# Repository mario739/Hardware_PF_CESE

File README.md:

###HARDWARE PROYECTO FINAL CESE

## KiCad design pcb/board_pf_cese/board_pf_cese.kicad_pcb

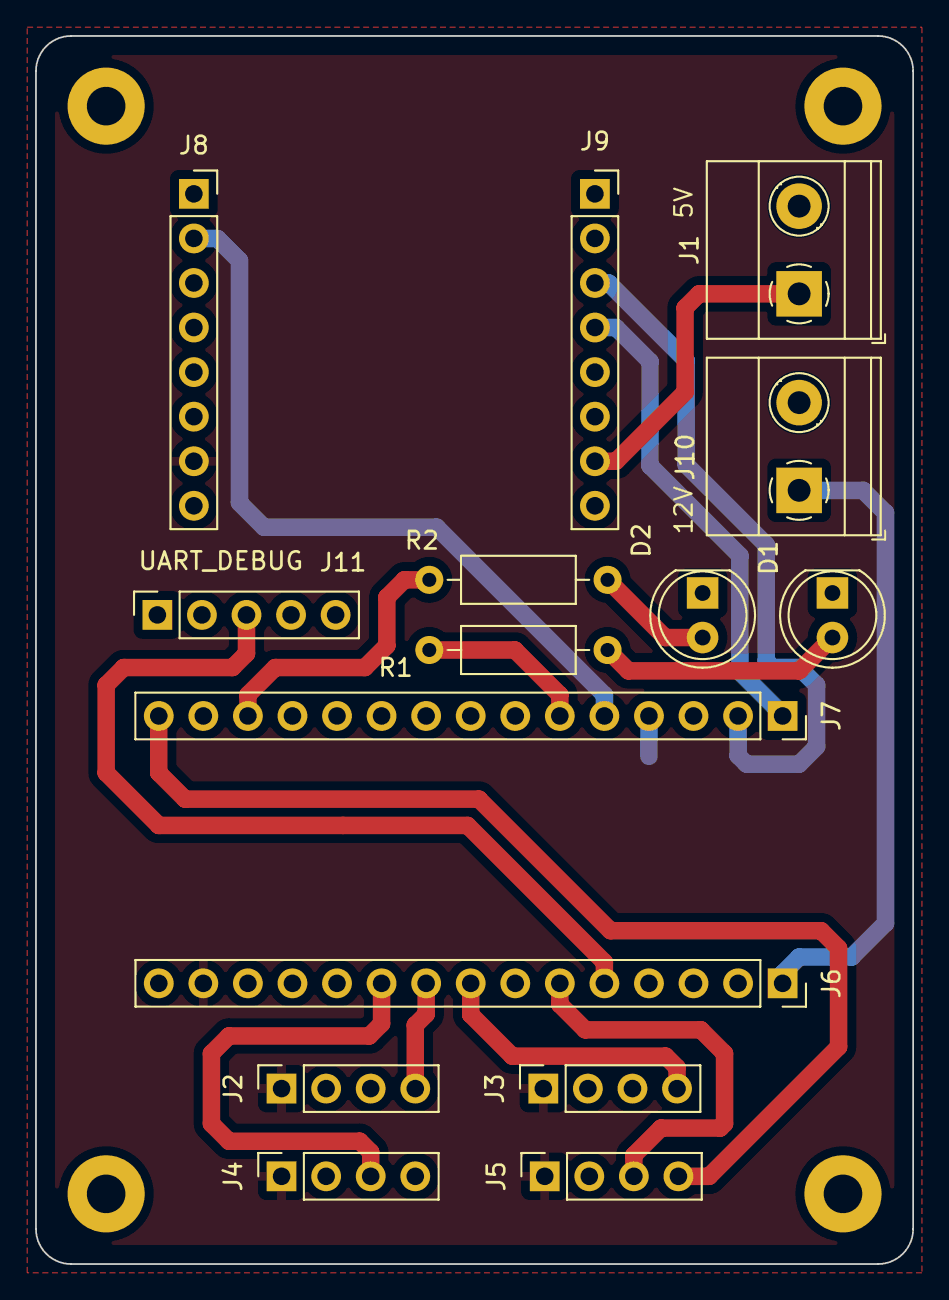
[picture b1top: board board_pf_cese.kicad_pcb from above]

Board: 2 copper layers, 50.0 x 70.0 mm, 15 parts (0 on the bottom side), 17 nets.

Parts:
D1, D2: LED; LED_D5.0mm
J1, J10: Screw_Terminal_01x02; TerminalBlock_Phoenix_MKDS-1,5-2_1x02_P5.00mm_Horizontal
J2, J3, J4, J5: Conn_01x04; PinSocket_1x04_P2.54mm_Vertical
J6, J7: Conn_01x15; PinSocket_1x15_P2.54mm_Vertical
J8, J9: Conn_01x08; PinSocket_1x08_P2.54mm_Vertical
J11: Conn_01x05; PinSocket_1x05_P2.54mm_Vertical
R1, R2: R; R_Axial_DIN0207_L6.3mm_D2.5mm_P10.16mm_Horizontal

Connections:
+3.3V: J2.1, J3.1, J4.1, J5.1, J6.14, J8.7
+5V: J1.1, J9.7
+12V: J6.1, J10.1
/M_RX: J7.1, J9.4
/M_TX: J7.2, J9.3
/OR: J7.5, J8.2
/SCL: J5.3, J6.6
/SDA: J5.4, J7.15
/SE: J7.13, R2.1
/SO: J7.6, R1.1
/UART2_TX: J6.5, J11.3
GND: D1.1 (K), D2.1 (K), J1.2, J2.2, J3.2, J4.2, J5.2, J6.2, J7.4, J8.8, J9.8, J10.2, J11.2
unnamed: D1.2 (A), R1.2
unnamed: D2.2 (A), R2.2
unnamed: J2.4, J6.9
unnamed: J3.4, J6.8
unnamed: J4.3, J6.10

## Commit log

2023-02-09 se creo el proyecto en kicad 6
2023-02-10 se realizo el esquematico de board
2023-02-10 colocacion de componentes en el pcb
2023-03-07 se agrego el archvo git ignore
2023-03-07 ignore
2023-03-07 se corrigio el error en el git ignore
2023-04-27 se redimensiono el tamaño del pcb
2023-07-20 ruteo con errores
2023-07-20 ruteo terminado
2023-08-24 se actualizo el metodo de alimentacion
2023-08-24 actualizacion esquematico
2023-08-25 se adiciono conn uart2 para debug
2023-08-25 corrigio posicionamiento del conn debug
2023-08-25 update esquematico
2023-09-11 update pcb
2023-09-11 finalizacion v1
